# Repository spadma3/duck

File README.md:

# Main software repository for Duckietown

This is the main software repository for [the Duckietown project][main]. It contains all software, as well as hardware projects.

- For an introduction to the project, see the site [duckietown.org][main].
- For extensive technical documentation, please refer to [the Duckiebooks][duckiebook].

[main]: http://duckietown.org/
[duckiebook]: http://docs.duckietown.org/

#### Branches

* `master17`: Stable 2017 branch
* `master18`: Current branch
* `master19`: will start in 2019

#### Continuous integration

See [the continuous integration console](https://circleci.com/gh/duckietown/Software/).

Master is now a protected branch. [See docs here](https://github.com/blog/2051-protected-branches-and-required-status-checks).

<table>
<thead>
    <tr><td>Branch</td><td>tests</td><td></td></tr>
</thead>
<tbody>
    <tr>
        <td> <code>master18</code> </td>
        <td>
            
        </td>
        <td>Merges to master are not allowed unless the tests pass. Master will always be green. </td>
    </tr>
</tbody>
</table>

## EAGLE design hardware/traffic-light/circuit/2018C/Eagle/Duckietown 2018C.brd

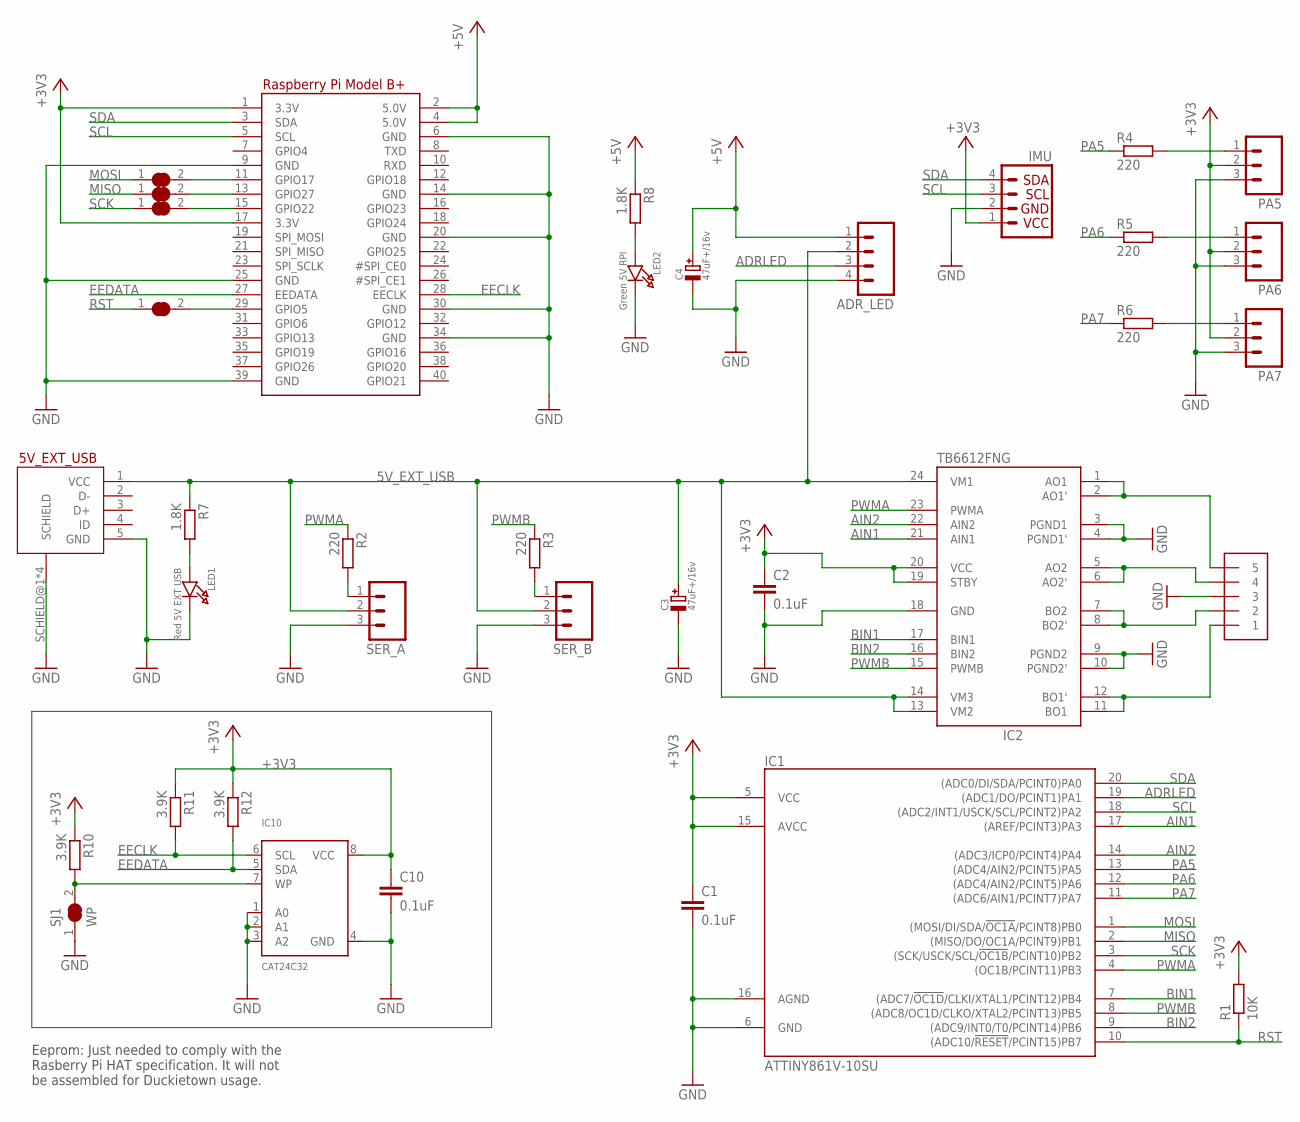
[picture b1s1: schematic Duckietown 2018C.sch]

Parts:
5V_EXT_USB: MICROUSBCON
ADR_LED: M04PTH; 1X04
C1, C2, C10: 0.1uF; C0603
C3, C4: 47uF+/16v; PANASONIC_C
IC1: ATTINY861V-10SU; SO20L
IC2: TB6612FNG; SSOP24
IC10: CAT24C32; SOIC8_150MIL
IMU: I2C_IMU_L3GD20H+LSM303; 1X04
LED1: Red 5V EXT USB; CHIPLED_0805_NOOUTLINE
LED2: Green 5V RPI; CHIPLED_0805_NOOUTLINE
MOTA: 1X5; 1X05-3.5MM
PA5, PA6, PA7: M03PTH; 1X03
R1: 10K; R0603
R2, R3, R4, R5, R6: 220; R0603
R7, R8: 1.8K; R0603
R10, R11, R12: 3.9K; R0603
RPI2: RASPBERRYPI_BPLUS_HATSLOTS; PI_HAT_SLOTS
RP_MISO: SOLDERJUMPER_CLOSED; SOLDERJUMPER_CLOSEDWIRE
RP_MOSI: SOLDERJUMPER_CLOSED; SOLDERJUMPER_CLOSEDWIRE
RP_RST: SOLDERJUMPER_CLOSED; SOLDERJUMPER_CLOSEDWIRE
RP_SCK: SOLDERJUMPER_CLOSED; SOLDERJUMPER_CLOSEDWIRE
SER_A: M03PTH; 1X03
SER_B: M03PTH; 1X03
SJ1: WP; SOLDERJUMPER_CLOSEDWIRE

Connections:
5V_EXT_USB: 5V_EXT_USB.1 (VCC), ADR_LED.2, C3.+, IC2.13 (VM2), IC2.14 (VM3), IC2.24 (VM1), R7.1, SER_A.2, SER_B.2
+3V3: C1.1, C2.1, C10.1, IC1.5 (VCC), IC1.15 (AVCC), IC2.19 (STBY), IC2.20 (VCC), IC10.8 (VCC), IMU.1, PA5.2, PA6.2, PA7.2, R1.2, R10.1, R11.1, R12.1, RPI2.1 (3.3V), RPI2.17 (3.3V)
+5V: ADR_LED.1, C4.+, R8.1, RPI2.2 (5.0V), RPI2.4 (5.0V)
ADRLED: ADR_LED.3, IC1.19 ((ADC1/DO/PCINT1)PA1)
AIN1: IC1.17 ((AREF/PCINT3)PA3), IC2.21 (AIN1)
AIN2: IC1.14 ((ADC3/ICP0/PCINT4)PA4), IC2.22 (AIN2)
BIN1: IC1.7 ((ADC7/!OC1D!/CLKI/XTAL1/PCINT12)PB4), IC2.17 (BIN1)
BIN2: IC1.9 ((ADC9/INT0/T0/PCINT14)PB6), IC2.16 (BIN2)
EECLK: IC10.6 (SCL), R11.2, RPI2.28 (EECLK)
EEDATA: IC10.5 (SDA), R12.2, RPI2.27 (EEDATA)
GND: 5V_EXT_USB.5 (GND), 5V_EXT_USB.SCHIELD@1 (SCHIELD), 5V_EXT_USB.SCHIELD@2 (SCHIELD), 5V_EXT_USB.SCHIELD@3 (SCHIELD), 5V_EXT_USB.SCHIELD@4 (SCHIELD), ADR_LED.4, C1.2, C2.2, C3.-, C4.-, C10.2, IC1.6 (GND), IC1.16 (AGND), IC2.3 (PGND1), IC2.4 (PGND1'), IC2.9 (PGND2), IC2.10 (PGND2'), IC2.18 (GND), IC10.1 (A0), IC10.2 (A1), IC10.3 (A2), IC10.4 (GND), IMU.2, LED1.C, LED2.C, MOTA.3, PA5.3, PA6.3, PA7.3, RPI2.6 (GND), RPI2.9 (GND), RPI2.14 (GND), RPI2.20 (GND), RPI2.25 (GND), RPI2.30 (GND), RPI2.34 (GND), RPI2.39 (GND), SER_A.3, SER_B.3, SJ1.1
MISO: IC1.2 ((MISO/DO/OC1A/PCINT9)PB1), RP_MISO.1
MOSI: IC1.1 ((MOSI/DI/SDA/!OC1A!/PCINT8)PB0), RP_MOSI.1
unnamed: LED2.A, R8.2
unnamed: IC2.5 (AO2), IC2.6 (AO2'), MOTA.4
unnamed: IC2.7 (BO2), IC2.8 (BO2'), MOTA.2
unnamed: LED1.A, R7.2
unnamed: IC10.7 (WP), R10.2, SJ1.2
unnamed: IC2.11 (BO1), IC2.12 (BO1'), MOTA.1
unnamed: IC2.1 (AO1), IC2.2 (AO1'), MOTA.5
unnamed: R2.2, SER_A.1
unnamed: PA5.1, R4.2
unnamed: R3.2, SER_B.1
unnamed: PA6.1, R5.2
unnamed: PA7.1, R6.2
unnamed: RPI2.15 (GPIO22), RP_SCK.2
unnamed: RPI2.13 (GPIO27), RP_MISO.2
unnamed: RPI2.11 (GPIO17), RP_MOSI.2
unnamed: RPI2.29 (GPIO5), RP_RST.2
PA5: IC1.13 ((ADC4/AIN2/PCINT5)PA5), R4.1
PA6: IC1.12 ((ADC4/AIN2/PCINT5)PA6), R5.1
PA7: IC1.11 ((ADC6/AIN1/PCINT7)PA7), R6.1
PWMA: IC1.4 ((OC1B/PCINT11)PB3), IC2.23 (PWMA), R2.1
PWMB: IC1.8 ((ADC8/OC1D/CLKO/XTAL2/PCINT13)PB5), IC2.15 (PWMB), R3.1
RST: IC1.10 ((ADC10/!RESET!/PCINT15)PB7), R1.1, RP_RST.1
SCK: IC1.3 ((SCK/USCK/SCL/!OC1B!/PCINT10)PB2), RP_SCK.1
SCL: IC1.18 ((ADC2/INT1/USCK/SCL/PCINT2)PA2), IMU.3, RPI2.5 (SCL)
SDA: IC1.20 ((ADC0/DI/SDA/PCINT0)PA0), IMU.4, RPI2.3 (SDA)

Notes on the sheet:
Eeprom: Just needed to comply with the Rasberry Pi HAT specification. It will not be assembled for Duckietown usage.

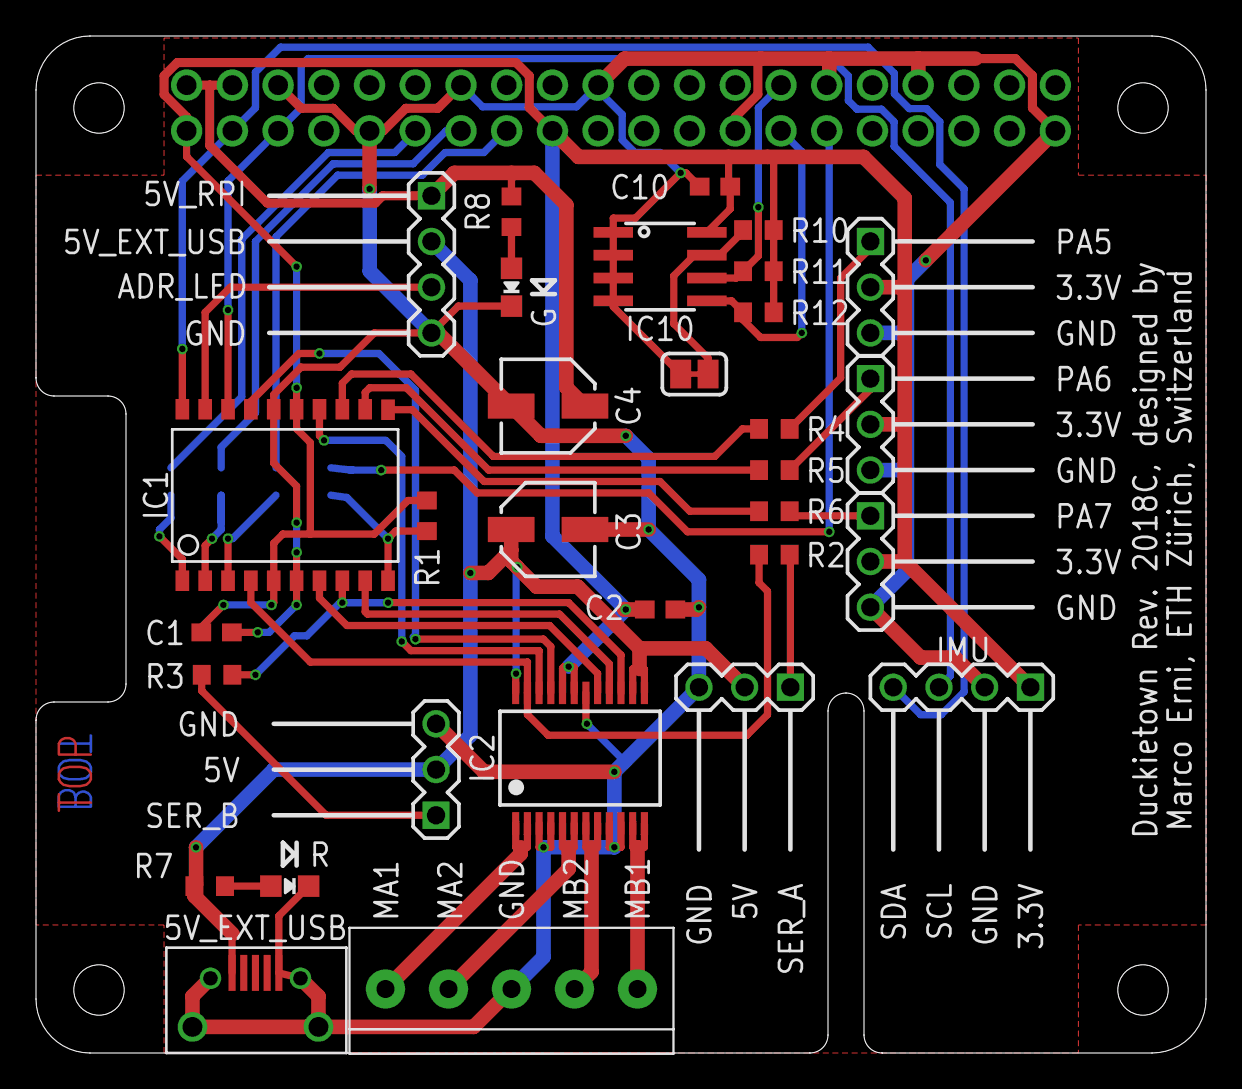
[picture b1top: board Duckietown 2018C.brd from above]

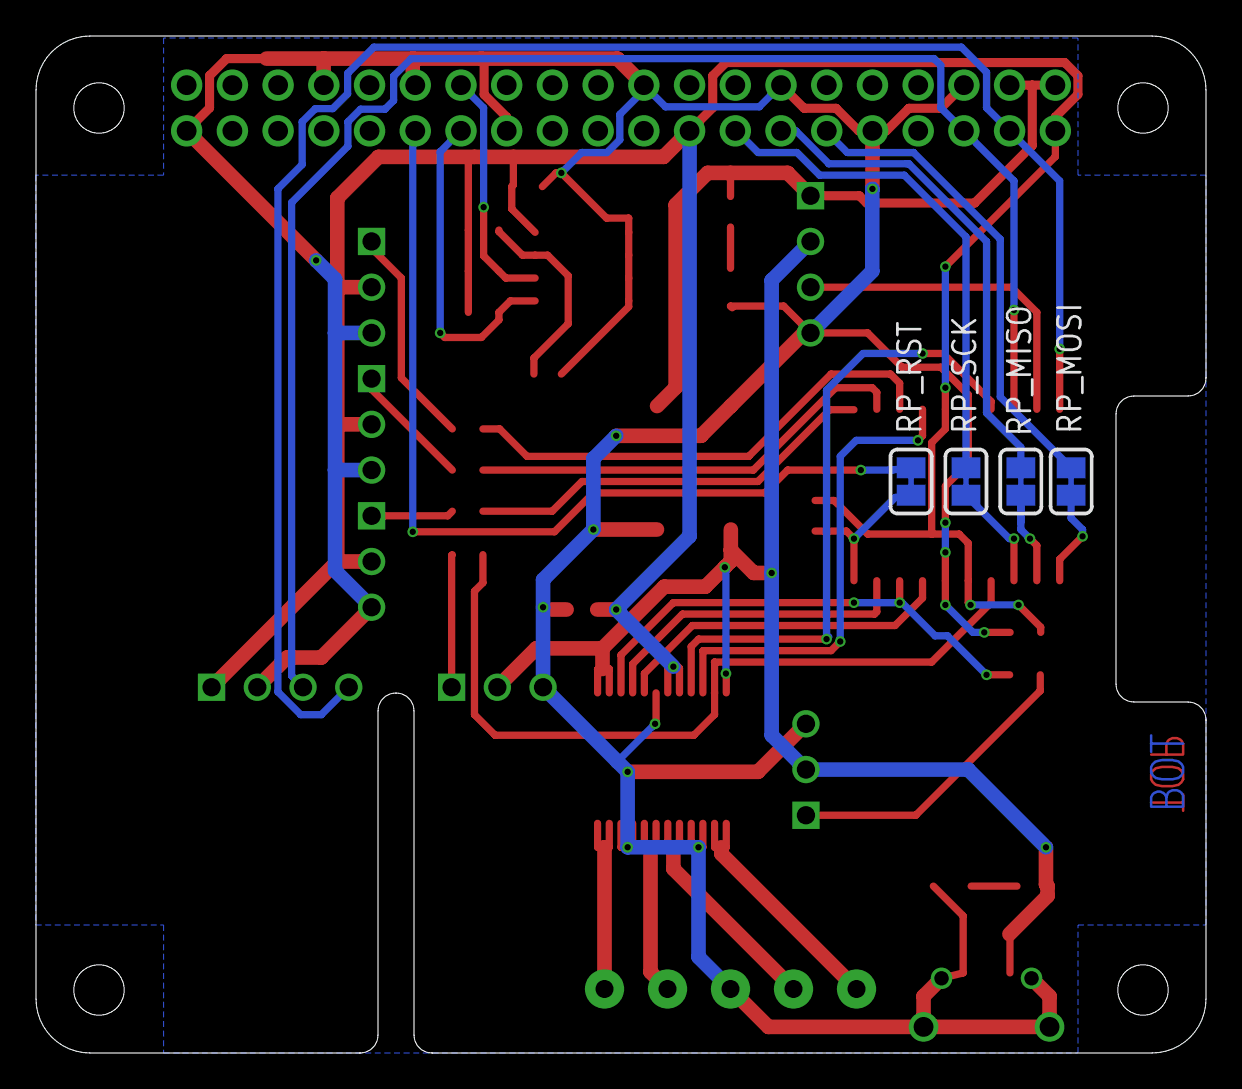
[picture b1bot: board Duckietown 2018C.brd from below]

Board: 2 copper layers, 65.0 x 56.5 mm, 36 parts (4 on the bottom side), 38 nets.

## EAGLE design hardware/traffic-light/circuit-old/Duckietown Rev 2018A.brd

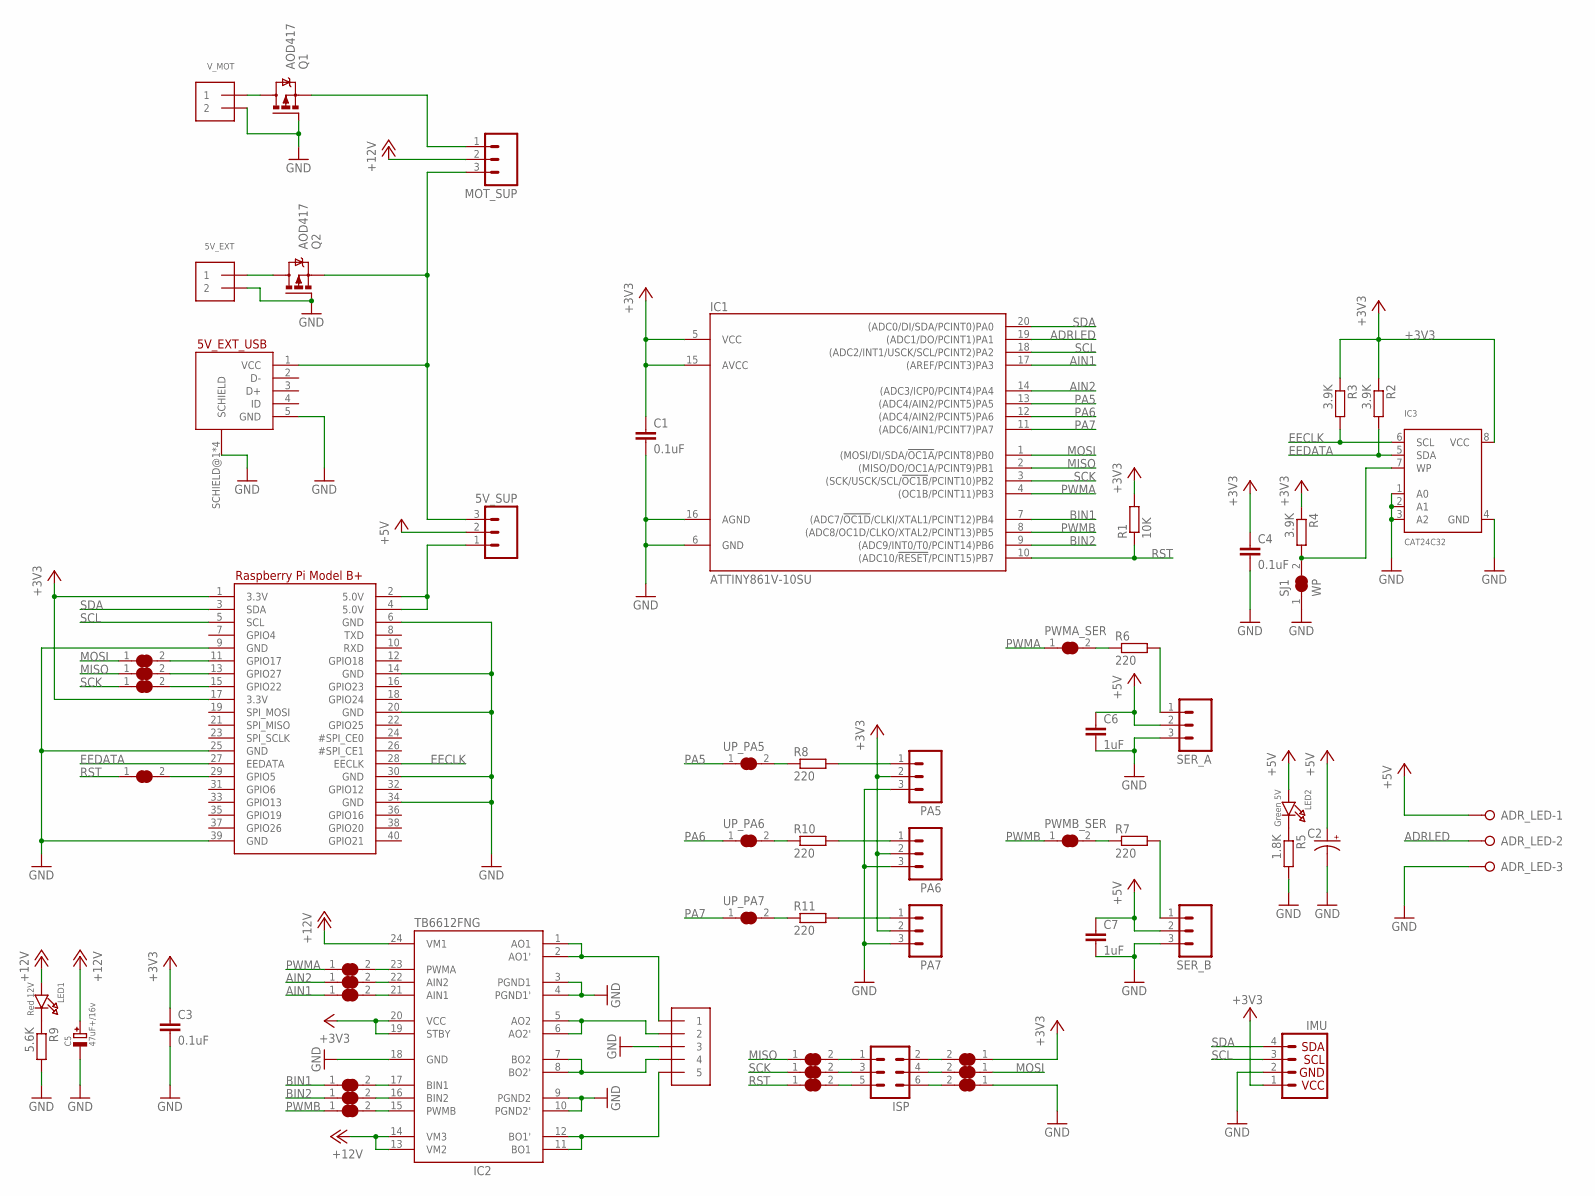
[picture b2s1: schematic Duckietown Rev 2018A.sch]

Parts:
5V_EXT: TERMBLOCK_1X2; TERMBLOCK_1X2-3.5MM
5V_EXT_USB: MICROUSBCON
5V_SUP: M03PTH; 1X03
ADR_LED: MPT0,5/3-2.54
AIN1, AIN2: SOLDERJUMPER_CLOSED; SOLDERJUMPER_CLOSEDWIRE
BIN1, BIN2: SOLDERJUMPER_CLOSED; SOLDERJUMPER_CLOSEDWIRE
C1, C3, C4: 0.1uF; C0603
C2: CPOL-USE3.5-8; E3,5-8
C5: 47uF+/16v; PANASONIC_C
C6, C7: 1uF; C0603
GND: SOLDERJUMPER_CLOSED; SOLDERJUMPER_CLOSEDWIRE
IC1: ATTINY861V-10SU; SO20L
IC2: TB6612FNG; SSOP24
IC3: CAT24C32; SOIC8_150MIL
IMU: I2C_IMU_L3GD20H+LSM303; 1X04
ISP: ML6
LED1: Red 12V; CHIPLED_0805_NOOUTLINE
LED2: Green 5V; CHIPLED_0805_NOOUTLINE
MISO: SOLDERJUMPER_CLOSED; SOLDERJUMPER_CLOSEDWIRE
MOSI: SOLDERJUMPER_CLOSED; SOLDERJUMPER_CLOSEDWIRE
MOTA: 1X5; 1X05-3.5MM
MOT_SUP: M03PTH; 1X03
PA5, PA6, PA7: M03PTH; 1X03
PWMA: SOLDERJUMPER_CLOSED; SOLDERJUMPER_CLOSEDWIRE
PWMA_SER: SOLDERJUMPER_CLOSED; SOLDERJUMPER_CLOSEDWIRE
PWMB: SOLDERJUMPER_CLOSED; SOLDERJUMPER_CLOSEDWIRE
PWMB_SER: SOLDERJUMPER_CLOSED; SOLDERJUMPER_CLOSEDWIRE
Q1, Q2: AOD417; D-PAK_TO252AA
R1: 10K; R0603
R2, R3, R4: 3.9K; R0603
R5: 1.8K; R0603
R6, R7, R8, R10, R11: 220; R0603
R9: 5.6K; R0603
RPI2: RASPBERRYPI_BPLUS_HATSLOTS; PI_HAT_SLOTS
RP_MISO: SOLDERJUMPER_CLOSED; SOLDERJUMPER_CLOSEDWIRE
RP_MOSI: SOLDERJUMPER_CLOSED; SOLDERJUMPER_CLOSEDWIRE
RP_RST: SOLDERJUMPER_CLOSED; SOLDERJUMPER_CLOSEDWIRE
RP_SCK: SOLDERJUMPER_CLOSED; SOLDERJUMPER_CLOSEDWIRE
RST: SOLDERJUMPER_CLOSED; SOLDERJUMPER_CLOSEDWIRE
SCK: SOLDERJUMPER_CLOSED; SOLDERJUMPER_CLOSEDWIRE
SER_A: M03PTH; 1X03
SER_B: M03PTH; 1X03
SJ1: WP; SOLDERJUMPER_CLOSEDWIRE
UP_PA5, UP_PA6, UP_PA7: SOLDERJUMPER_CLOSED; SOLDERJUMPER_CLOSEDWIRE
VCC: SOLDERJUMPER_CLOSED; SOLDERJUMPER_CLOSEDWIRE
V_MOT: TERMBLOCK_1X2; TERMBLOCK_1X2-3.5MM

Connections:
5V_RPI: 5V_SUP.1, RPI2.2 (5.0V), RPI2.4 (5.0V)
+3V3: C1.1, C3.1, C4.1, IC1.5 (VCC), IC1.15 (AVCC), IC2.19 (STBY), IC2.20 (VCC), IC3.8 (VCC), IMU.1, PA5.2, PA6.2, PA7.2, R1.2, R2.1, R3.1, R4.1, RPI2.1 (3.3V), RPI2.17 (3.3V), VCC.1
+5V: 5V_SUP.2, ADR_LED.1, C2.+, C6.1, C7.1, LED2.A, SER_A.2, SER_B.2
+12V: C5.+, IC2.13 (VM2), IC2.14 (VM3), IC2.24 (VM1), LED1.A, MOT_SUP.2
ADRLED: ADR_LED.2, IC1.19 ((ADC1/DO/PCINT1)PA1)
AIN1: AIN1.1, IC1.17 ((AREF/PCINT3)PA3)
AIN2: AIN2.1, IC1.14 ((ADC3/ICP0/PCINT4)PA4)
BIN1: BIN1.1, IC1.7 ((ADC7/!OC1D!/CLKI/XTAL1/PCINT12)PB4)
BIN2: BIN2.1, IC1.9 ((ADC9/INT0/T0/PCINT14)PB6)
EECLK: IC3.6 (SCL), R3.2, RPI2.28 (EECLK)
EEDATA: IC3.5 (SDA), R2.2, RPI2.27 (EEDATA)
GND: 5V_EXT.2, 5V_EXT_USB.5 (GND), 5V_EXT_USB.SCHIELD@1 (SCHIELD), 5V_EXT_USB.SCHIELD@2 (SCHIELD), 5V_EXT_USB.SCHIELD@3 (SCHIELD), 5V_EXT_USB.SCHIELD@4 (SCHIELD), ADR_LED.3, C1.2, C2.-, C3.2, C4.2, C5.-, C6.2, C7.2, GND.1, IC1.6 (GND), IC1.16 (AGND), IC2.3 (PGND1), IC2.4 (PGND1'), IC2.9 (PGND2), IC2.10 (PGND2'), IC2.18 (GND), IC3.1 (A0), IC3.2 (A1), IC3.3 (A2), IC3.4 (GND), IMU.2, MOTA.3, PA5.3, PA6.3, PA7.3, Q1.1 (G), Q2.1 (G), R5.2, R9.2, RPI2.6 (GND), RPI2.9 (GND), RPI2.14 (GND), RPI2.20 (GND), RPI2.25 (GND), RPI2.30 (GND), RPI2.34 (GND), RPI2.39 (GND), SER_A.3, SER_B.3, SJ1.1, V_MOT.2
MISO: IC1.2 ((MISO/DO/OC1A/PCINT9)PB1), MISO.1, RP_MISO.1
MOSI: IC1.1 ((MOSI/DI/SDA/!OC1A!/PCINT8)PB0), MOSI.1, RP_MOSI.1
unnamed: Q1.4 (D), V_MOT.1
unnamed: IC2.5 (AO2), IC2.6 (AO2'), MOTA.2
unnamed: IC2.7 (BO2), IC2.8 (BO2'), MOTA.4
unnamed: LED1.C, R9.1
unnamed: 5V_EXT.1, Q2.4 (D)
unnamed: LED2.C, R5.1
unnamed: IC3.7 (WP), R4.2, SJ1.2
unnamed: IC2.11 (BO1), IC2.12 (BO1'), MOTA.5
unnamed: IC2.1 (AO1), IC2.2 (AO1'), MOTA.1
unnamed: MOT_SUP.1, Q1.3 (S)
unnamed: R6.2, SER_A.1
unnamed: PA5.1, R8.2
unnamed: R7.2, SER_B.1
unnamed: PA6.1, R10.2
unnamed: PA7.1, R11.2
unnamed: IC2.23 (PWMA), PWMA.2
unnamed: AIN2.2, IC2.22 (AIN2)
unnamed: AIN1.2, IC2.21 (AIN1)
unnamed: BIN1.2, IC2.17 (BIN1)
unnamed: BIN2.2, IC2.16 (BIN2)
unnamed: IC2.15 (PWMB), PWMB.2
unnamed: ISP.1, MISO.2
unnamed: ISP.3, SCK.2
unnamed: ISP.5, RST.2
unnamed: ISP.4, MOSI.2
unnamed: GND.2, ISP.6
unnamed: ISP.2, VCC.2
unnamed: R10.1, UP_PA6.2
unnamed: PWMB_SER.2, R7.1
unnamed: PWMA_SER.2, R6.1
unnamed: R8.1, UP_PA5.2
unnamed: RPI2.15 (GPIO22), RP_SCK.2
unnamed: RPI2.13 (GPIO27), RP_MISO.2
unnamed: RPI2.11 (GPIO17), RP_MOSI.2
unnamed: RPI2.29 (GPIO5), RP_RST.2
unnamed: R11.1, UP_PA7.2
PA5: IC1.13 ((ADC4/AIN2/PCINT5)PA5), UP_PA5.1
PA6: IC1.12 ((ADC4/AIN2/PCINT5)PA6), UP_PA6.1
PA7: IC1.11 ((ADC6/AIN1/PCINT7)PA7), UP_PA7.1
PWMA: IC1.4 ((OC1B/PCINT11)PB3), PWMA.1, PWMA_SER.1
PWMB: IC1.8 ((ADC8/OC1D/CLKO/XTAL2/PCINT13)PB5), PWMB.1, PWMB_SER.1
RST: IC1.10 ((ADC10/!RESET!/PCINT15)PB7), R1.1, RP_RST.1, RST.1
SCK: IC1.3 ((SCK/USCK/SCL/!OC1B!/PCINT10)PB2), RP_SCK.1, SCK.1
SCL: IC1.18 ((ADC2/INT1/USCK/SCL/PCINT2)PA2), IMU.3, RPI2.5 (SCL)
SDA: IC1.20 ((ADC0/DI/SDA/PCINT0)PA0), IMU.4, RPI2.3 (SDA)
VCC: 5V_EXT_USB.1 (VCC), 5V_SUP.3, MOT_SUP.3, Q2.3 (S)

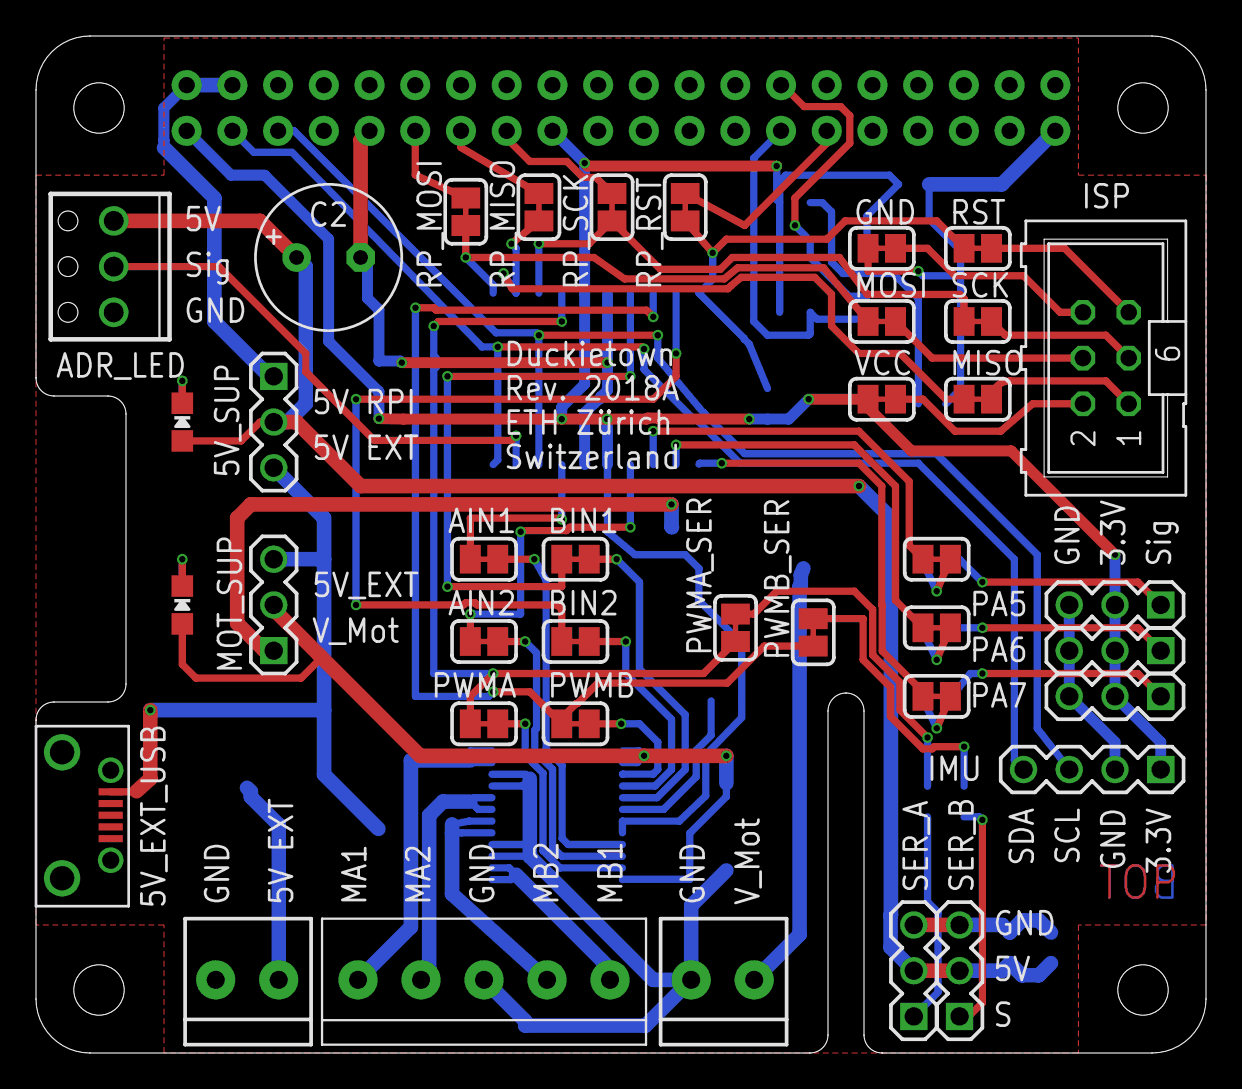
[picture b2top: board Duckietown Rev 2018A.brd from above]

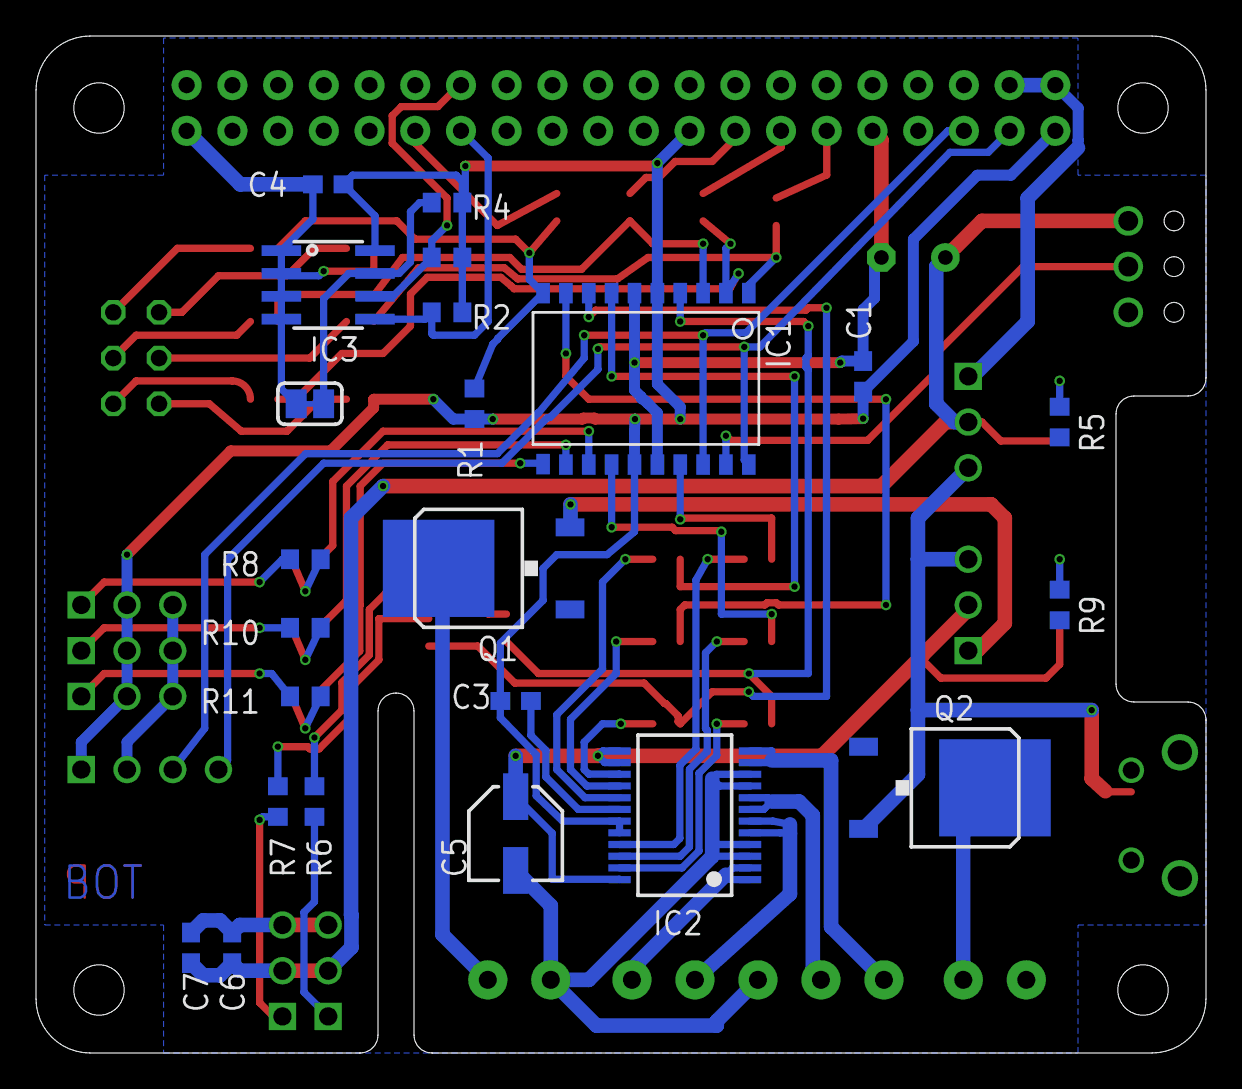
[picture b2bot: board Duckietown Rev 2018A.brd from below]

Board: 2 copper layers, 65.0 x 56.5 mm, 62 parts (23 on the bottom side), 60 nets.

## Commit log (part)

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2018-08-07 add more Localization Tags to the database
2018-08-07 fixed bug
2018-08-07 changed freqs
2018-08-08 freq change test
2018-08-08 freq test
2018-08-08 Add 40 Megabots to ApriltagsDB. Overwrite a few Street Signs
2018-08-08 Raise Exception if Tag is not in the Database
2018-08-10 Add debugging output
2018-08-10 Add Localization Tags to DB, overwrite of streetsigns
2018-08-13 Limit maximum size of the sended array to three poses (Ethernet limitation)
2018-08-13 remove debugging output
2018-08-13 Set default Buffer size to 1024
2018-08-13 Limit packet size to three poses
2018-08-13 Use current time instead of latest common time for tf transformation
2018-08-13 Make Output human readable
2018-08-13 Set map parameter at server
2018-08-14 debugging
2018-08-14 added freqs
2018-08-14 fixed fft_peak_freq
2018-08-14 Always generate unique output file
2018-08-14 revert freqs
2018-08-14 test half_freq_dist
2018-08-14 Added shaky maneveur
2018-08-14 fix?
2018-08-14 fix half freq dist
2018-08-15 fft fix
2018-08-15 fix fft_fs
2018-08-15 latency
2018-08-16 changed publishing order in coordinator node
2018-08-16 added two missing cases in coordinator node
2018-08-16 fixed keep_calm case
2018-08-16 commented some not needed parts
2018-08-16 using loginfo instead print for debug messages
2018-08-16 deleted some not needed parts
2018-08-16 commented some parts
2018-08-16 fixed loginfo formatting
2018-08-17 Show Apriltag detection image for debugging
2018-08-17 Use timer instead of manual counter
2018-08-17 no error while running GUI but no output while getting watchtower data
2018-08-17 added blockly controller for wheels
2018-08-18 first ok version
2018-08-20 add React area
2018-08-20 Beautify
2018-08-20 Allow Redundant Poses
2018-08-20 fix the connection between GUI and calibration node
2018-08-20 sent correct poses (ALL poses)
2018-08-20 chmod on node
2018-08-20 Remove Bug
2018-08-20 correct typo
2018-08-20 Add waittime after GUI finds a path
2018-08-20 Debugging outpu to see which tag pairs are found
2018-08-22 Improved TCP communication
2018-08-22 Bugs fixin
2018-08-23 Resolve typo
2018-08-23 Easy readable output
2018-08-23 Update Watchtowers in map
2018-08-24 Added files for network change
2018-08-24 correct camera matrix mid point problem
2018-08-24 use try except to fix the problem can't find frame
2018-08-24 solve tree problem, every tag will be in the link
2018-08-24 always open GUI, correct map coordination (not final)
2018-08-27 Adding Multi pose optimization node
2018-08-28 pose optimization polishing
2018-08-29 Add tile type to GlobalPose msg.
2018-08-29 Done with pose optimization, waiting for testing
2018-08-29 Add node for tile conversion
2018-08-29 Add script to login to all watchtowers at one
2018-08-29 commit some important map file. As well final update
2018-08-29 Merlin trys coding
2018-08-30 Read Tiles from map data
2018-08-31 Add Launchfile for watchtower including trafficlight
2018-08-31 Removed small bug in data collection
2018-08-31 Integrate treafficlight to readme
2018-08-31 Add trafficlight to readme
2018-09-01 add map with calibrated tags
2018-09-04 untracked files left on megabot06
2018-09-04 added option to turn off priority protocol through launch files
2018-09-04 added graphviz in requirements.txt
2018-09-04 launch file arg added
2018-09-06 adding new flashing files for microcontroller
2018-09-08 Breandan + caffeine (#336)
    * Initial Dockerfile
    * Move duckietown/software into build process
    * Add Docker stuff
    * move dockerfile to project root directory
    * remove rosdep init/update
    * refactor buildscript
2018-09-08 Switch readme to markdoen
2018-09-08 Fix conflict
2018-09-09 polish
2018-09-09 major cleanup
2018-09-09 more cleanup
2018-09-09 fixing
2018-09-09 cleanup
2018-09-09 updated tags in the duckietown map
2018-09-09 README for easy_logs missing
2018-09-09 spurious
2018-09-09 testing
2018-09-09 Revert "Fixed bug"
    This reverts commit 3e0ee33d987937d7b1a5fc4f9b6126e5807c00ea.
2018-09-09 Switch for unicorn instersection
2018-09-10 adding Localization apriltags
2018-09-10 new apriltags list
2018-09-12 Correctly Average Quaternions
2018-09-13 [ADDED] ICRA experiments launch file.
2018-09-14 Evaluation Data and Tools
2018-09-14 Test data from calibration
2018-09-14 [ADDED] ICRA experiments debugging
2018-09-16 re-adding lane filter version
2018-09-16 spurious file
2018-09-17 do not force ROS_MASTER_URI and accept ROS_MASTER env variable
2018-09-17 Generating Evaluation Plots for local poses
2018-09-18 clean up package and launch file, must specify map name while launching auto-localization
2018-09-18 Add map
2018-09-18 Evaluation for System Calibration
2018-09-18 use `hostname -I` instead of attempting to parse `ifconfig`
2018-09-19 spurious submodule
2018-09-20 upgrade pip for matplotlib
2018-09-21 use normal size, no crop, no resize
2018-09-21 final touch watchtower side
2018-09-21 final touch laptop side
2018-09-21 save changes in evaluation
2018-09-21 Add script to correctly average quaternions
2018-09-22 set ROS_MASTER to localhost by default, exit if unreachable
2018-09-23 Update README.md
    typos
2018-09-23 fix error with ROS_MASTER_URI
2018-09-24 updated line test
2018-09-24 set docker env variables in docker/env.sh
2018-09-24 add mDNS name to /etc/hosts within Docker so remote clients can reach us via *.local
2018-09-25 add ROS_MASTER_IP to /etc/hosts for remote container access
2018-09-25 removing obsolete hardware files
2018-09-25 adding brackets
2018-09-25 add local build directories to .dockerignore
2018-09-25 add optional DUCKIEBOT_NAME and DUCKIEBOT_IP env variables
2018-09-26 assume master node is always on the Duckiebot when using Docker
2018-09-26 reverse conditional (both variables should be set)
2018-09-26 ! -z for compatibility with older bash versions
2018-09-26 fix ROS_MASTER_URI as it is set during the Docker build
2018-09-27 make exposure time adjustable by config file
2018-09-27 duckiebotname.local
2018-09-27 removing copying default to hostname
2018-09-27 DUCKIEBOT_NAME.local is not accessible from the duckiebot
2018-09-28 modify exposure time in config file
2018-09-28 tcp node name correction
2018-09-28 Installation of Python dependencies. Bypass rpi-ros-kinetic-dev.
2018-09-28 update requirements for picamera
2018-09-28 Updating Dockerfile to use master18 deps
2018-10-02 updated docker file
2018-10-02 done
2018-10-03 cleaning up master launch
2018-10-03 replacing the publishing of the belief image that got removed somewhere along the way
2018-10-03 first commit, removed yaml maps
2018-10-03 Turn on obst avoidance
2018-10-04 add Taiwanese feature and try manual put tags
2018-10-04 add bot detector to pipeline
2018-10-05 separated the launch file
2018-10-06 X-build must fully enclose all RUN instructions
2018-10-06 added calibration folder under 05-teleop
2018-10-06 Fixed topic names and remapping
2018-10-06 obst_avoidance test
2018-10-06 obst avoid test
2018-10-06 fix wrong placement of commands
2018-10-06 Docker utils
2018-10-08 optim start
2018-10-11 bot detection code
2018-10-11 plots
2018-10-11 pickle to save/load data for faster testing of optimization routine.
2018-10-12 test setup to ssh into watchtowers added
2018-10-12 testing map added, to be changed
2018-10-12 manual obstacle avoidance and additional virjoy command
2018-10-13 optimization is refactored for use of min and obj functions
2018-10-13 refactoring is completed to include the sine experiment as well
2018-10-13 Replaced odeint with forwardEuler fn implementation.
2018-10-13 plots for sine + obj fn seperated for sine
2018-10-14 plot combined params predictions
2018-10-14 combined cf
2018-10-14 fixed a bug in cf
2018-10-15 change csv storage destination, only use localization tag as reference tag
2018-10-15 basic change
2018-10-15 bug fixes
2018-10-15 don't sent message if there's no Duckiebot
2018-10-15 some correction of local ap tag
2018-10-16 reverted
2018-10-16 vehicle avoidance causing problems!
2018-10-16 vehicle avoidance causing problems but cannot be disabled otherwise whole pipeline is dead!
2018-10-16 load/save
2018-10-17 fixed a bug in loading default camera_intrinsic file
2018-10-18 Make compatable with Melodic
2018-10-18 negation of yaw rate is required due to a bug in the code
2018-10-25 checkout
2018-10-30 fixed bug on launchfile
2018-11-01 draw Duckiepath, save csv to csv folder
2018-11-01 Use black background
2018-11-01 added auto-localization package
2018-11-05 base model class + a gain-trim model
2018-11-06 choose multiple trajectory
2018-11-06 fix for lane_filter bug
2018-11-06 getting closer to fixing this
2018-11-07 adding A3 camera calibration pattern source file
    this is the current (DB18) camera calibration pattern, on A3 format
2018-11-09 updating logging infrastructure
2018-11-09 script: measurements in robot cf
2018-11-09 changing default logging path
2018-11-10 Update lane_controller_node.py
    Addresses #381
2018-11-10 small fix to log launch file
2018-11-10 renaming
2018-11-10 making backwards compatible with non-docker
2018-11-10 changing default path to match new instructions
2018-11-11 some work on rovot cf
2018-11-14 do not overwrite ROS_MASTER_URI if set externally
2018-11-15 added decoder_param_file_name in camera.launch
2018-11-16 intergrate reading two kinds of map file
2018-11-16 integrate both format of map (manually input and input by automatically calibration)
2018-11-16 correct absolute from relative position
2018-11-16 correct y axis while drawing the map
2018-11-16 correct the pixel to click on robot, slove the bug that optimization node wont send bot id
2018-11-16 removed veh from topic name
2018-12-04 avahi and line detectors params
2018-12-06 start the avahi service automatically
2018-12-07 update map
2018-12-08 straight
2019-01-15 modify the size of rectify images
2019-01-17 add trigger for publishing apriltags
2019-01-21 isam tag collection
2019-01-21 add trigger to tag collection node
2019-01-21 fix library problem
2019-02-04 map at TTIC created
2019-02-04 python version of odom
2019-02-04 stop publisher
2019-02-04 odometry template copied
2019-02-04 switching to python
2019-02-04 gps broadcaster untested version added
2019-02-04 stopping
2019-02-04 stop
2019-02-04 new positions for signs added
2019-02-04 odometry improved
2019-02-04 config msg type set up
2019-02-04 visual-gps to tf broadcaster
2019-02-04 new lcm_types; control center node; duckiebot node
2019-02-04 increased perception time
2019-02-04 activating event communication
2019-02-04 reaction distance implemented
2019-02-04 mcomp stop experiment service; minor
2019-02-04 duckiebot node added
2019-02-04 lcm_types built
2019-02-04 avoid republishing event
2019-02-04 event publication implemented
2019-02-04 added is_stopped to duckiebot node
2019-02-04 bug fixed
2019-02-04 improvements; implementing viz
2019-02-04 viz functions added
2019-02-04 hack to recover UDP dropped packets for blocking messages
2019-02-04 added default to reaction_radius
2019-02-04 blind stopping disabled
2019-02-04 bug fixed: the distance from the sender was not correct
2019-02-04 allow republish implemented
2019-02-04 bug fixed, the vehicle location of the sender was not set
2019-02-04 added some untied verbose prints
2019-02-04 add 'default' machine
2019-02-13 add car conmmend control for Duckietown demo
2019-02-15 add jupyter car commend node
2019-02-18 evil tab
2019-02-18 trying another way
2019-02-20 fix
    fix for #396
2019-02-21 created test_push file
2019-02-21 A Large AprilTag for System Identification Demo
2019-02-22 Revert "Update requirements.txt"
2019-02-25 changed inverse kinematics node
2019-02-25 check if changeing the parameter names breaks stuff
2019-02-25 check if callback is the problem
2019-02-25 rename stuff
2019-02-25 back to zero
2019-02-25 back to zero2
2019-02-25 reset
2019-02-25 change params
2019-02-25 hardcode baseline
2019-02-25 without getParam()
2019-02-25 hardcode in getParam
2019-02-25 params defined, no methods defined
2019-02-25 publish gamma for the first time
2019-02-25 hello as loginfo
2019-02-25 update dep
2019-02-26 add a same master version of localization
2019-02-26 new map
2019-03-06 first code to be executed on the duckiebot
2019-03-06 push first testrun code
2019-03-07 version of successful testrun on megabot23

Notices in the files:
parts and their libraries:
microbuilder: This work is placed in the public domain, and may be freely used for commercial and non-commercial work with the following conditions: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
